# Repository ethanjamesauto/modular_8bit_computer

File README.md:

# Modular 8-bit Computer
This is the repository for an 8-bit computer system that is built using cards with a standardized interface. 

* [CPU card](processor_attempt_1)
* [Protoboard card](smaller_card_for_74_series)
  * This card contains an onboard clock generator, address and data registers/buffers, and a protoboard area for testing designs.
* [Bus interface modeling](digital)

Here's an example of a card:

## Current Bus Specification
```verilog
// The main bus wires (32+8=40 wires total)
// On the bus connector, all buses have LSBs closer to the power pins and MSBs farther away
wire VCC_5V;
wire GND;
wire clk;			      // generated by motherboard clock generator
wire rst_n;			    // probably a button on the motherboard
wire VCC_3V3;
wire we_n;			      // active LOW
wire oe_n;			      // active LOW
wire int_n;			    // pulled up by motherboard; driven down by any peripheral (could be used for interrupts)
wire [7:0] data;
wire [15:0] addr;	  // 64k address space is suppored by default. More address bits may be added later
wire [7:0] aux_bus;
```

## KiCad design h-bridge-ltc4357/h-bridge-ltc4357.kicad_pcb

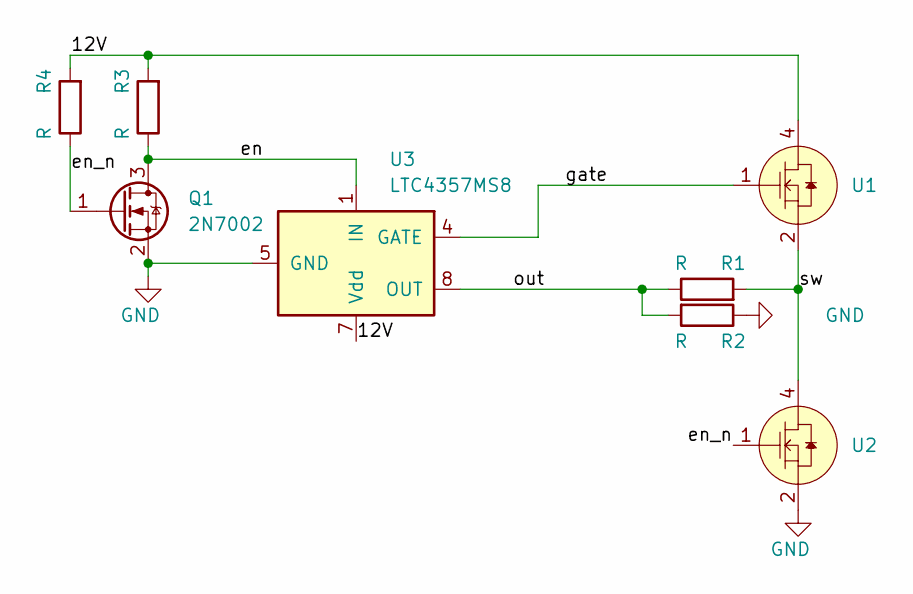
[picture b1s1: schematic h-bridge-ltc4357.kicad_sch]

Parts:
Q1: 2N7002; SOT-23
R1, R2, R3, R4: R; R_0603_1608Metric_Pad0.98x0.95mm_HandSolder
U1, U2: TO-263-6
U3: LTC4357MS8; MSOP-8_3x3mm_P0.65mm

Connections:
/12V: R3.2, R4.2, U1.4, U3.7 (Vdd)
/en: Q1.3 (D), R3.1, U3.1 (IN)
/en_n: Q1.1 (G), R4.1, U2.1
/gate: U1.1, U3.4 (GATE)
/out: R1.1, R2.2, U3.8 (OUT)
/sw: R1.2, U1.2, U1.3, U1.5, U1.6, U1.7, U2.4
GND: Q1.2 (S), R2.1, U2.2, U2.3, U2.5, U2.6, U2.7, U3.5 (GND)

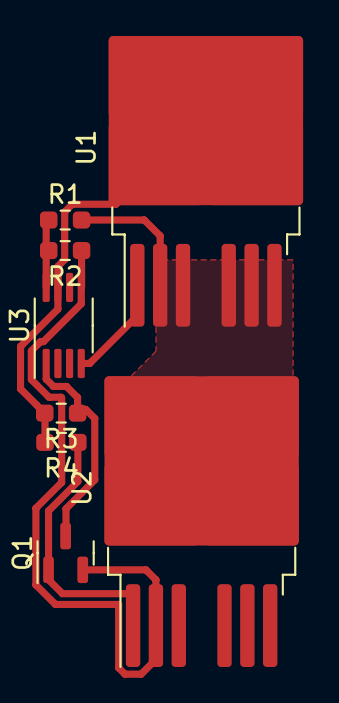
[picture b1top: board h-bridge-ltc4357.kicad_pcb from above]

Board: 2 copper layers, 8 parts (0 on the bottom side), 7 nets.

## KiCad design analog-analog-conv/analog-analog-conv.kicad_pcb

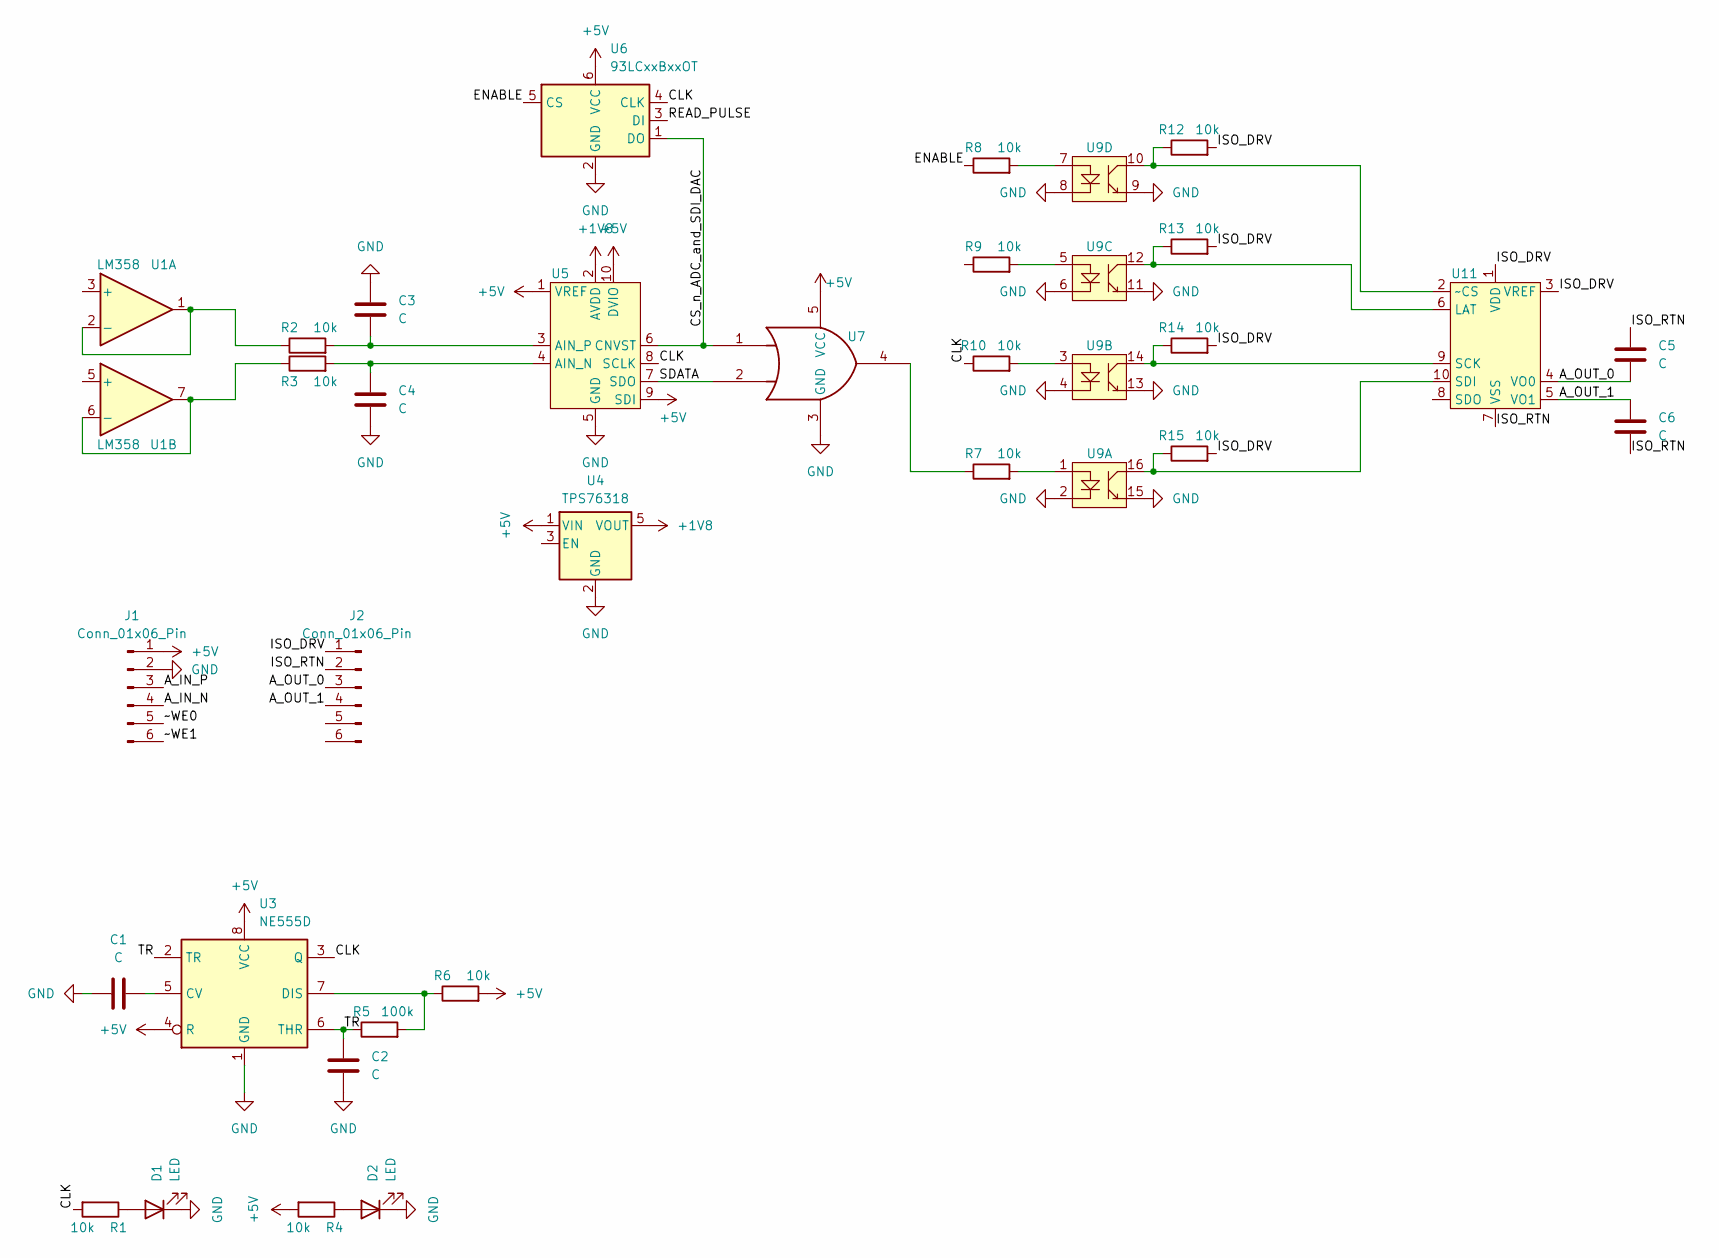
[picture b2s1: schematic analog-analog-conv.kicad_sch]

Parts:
C1, C2, C3, C4, C5, C6: C; C_0603_1608Metric_Pad1.08x0.95mm_HandSolder
D1, D2: LED; LED_0603_1608Metric_Pad1.05x0.95mm_HandSolder
J1, J2: Conn_01x06_Pin; PinHeader_1x06_P2.54mm_Vertical
R1, R2, R3, R4, R6, R7, R8, R9, R10, R12, R13, R14, R15: 10k; R_0603_1608Metric_Pad0.98x0.95mm_HandSolder
R5: 100k; R_0603_1608Metric_Pad0.98x0.95mm_HandSolder
U1: LM358; SOIC-8_3.9x4.9mm_P1.27mm
U3: NE555D; SOIC-8_3.9x4.9mm_P1.27mm
U4: TPS76318; SOT-23-5
U5: MCP33141D; MSOP-10_3x3mm_P0.5mm
U6: 93LCxxBxxOT; SOT-23-6
U7: 74LVC1G32; SOT-23-5_HandSoldering
U9: SOIC-16_4.55x10.3mm_P1.27mm
U11: MSOP-10_3x3mm_P0.5mm

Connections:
+1V8: U4.5 (VOUT), U5.2 (AVDD)
+5V: J1.1, R4.2, R6.2, U3.4 (R), U3.8 (VCC), U4.1 (VIN), U5.1 (VREF), U5.9 (SDI), U5.10 (DVIO), U6.6 (VCC), U7.5 (VCC)
/A_IN_N: J1.4
/A_IN_P: J1.3
/A_OUT_0: C5.1, J2.3, U11.4 (VO0)
/A_OUT_1: C6.2, J2.4, U11.5 (VO1)
/CLK: R1.2, R10.1, U3.3 (Q), U5.8 (SCLK), U6.4 (CLK)
/CS_n_ADC_and_SDI_DAC: U5.6 (CNVST), U6.1 (DO), U7.1
/ENABLE: R8.1, U6.5 (CS)
/ISO_DRV: J2.1, R12.2, R13.2, R14.2, R15.2, U11.1 (VDD), U11.3 (VREF)
/ISO_RTN: C5.2, C6.1, J2.2, U11.7 (VSS)
/READ_PULSE: U6.3 (DI)
/SDATA: U5.7 (SDO), U7.2
/TR: C2.1, R5.1, U3.2 (TR), U3.6 (THR)
/~WE0: J1.5
/~WE1: J1.6
GND: C1.1, C2.2, C3.2, C4.1, D1.1 (K), D2.1 (K), J1.2, U3.1 (GND), U4.2 (GND), U5.5 (GND), U6.2 (GND), U7.3 (GND), U9.2, U9.4, U9.6, U9.8, U9.9, U9.11, U9.13, U9.15
unnamed: D1.2 (A), R1.1
unnamed: D2.2 (A), R4.1
unnamed: R7.1, U7.4
unnamed: R7.2, U9.1
unnamed: R8.2, U9.7
unnamed: R9.2, U9.5
unnamed: R10.2, U9.3
unnamed: R2.1, U1.1, U1.2 (-)
unnamed: R3.1, U1.6 (-), U1.7
unnamed: C1.2, U3.5 (CV)
unnamed: R5.2, R6.1, U3.7 (DIS)
unnamed: C4.2, R3.2, U5.4 (AIN_N)
unnamed: C3.1, R2.2, U5.3 (AIN_P)
unnamed: R13.1, U9.12, U11.6 (LAT)
unnamed: R14.1, U9.14, U11.9 (SCK)
unnamed: R15.1, U9.16, U11.10 (SDI)
unnamed: R12.1, U9.10, U11.2 (~CS)

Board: 2 copper layers, 32 parts (7 on the bottom side), 29 nets, no tracks yet.

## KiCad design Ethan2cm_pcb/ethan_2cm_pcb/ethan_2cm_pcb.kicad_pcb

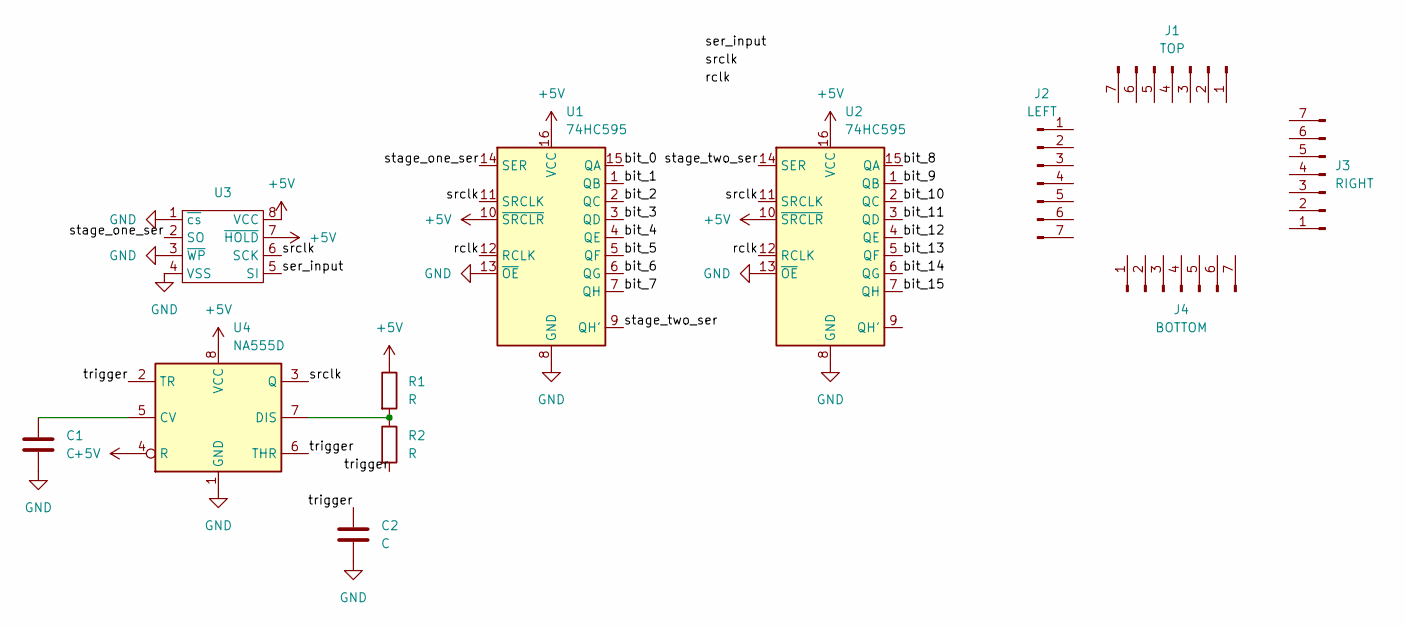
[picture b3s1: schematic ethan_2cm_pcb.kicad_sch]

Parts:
C1, C2: C; C_0603_1608Metric
J1: TOP; PinHeader_1x07_P2.54mm_Vertical
J2: LEFT; PinHeader_1x07_P2.54mm_Vertical
J3: RIGHT; PinHeader_1x07_P2.54mm_Vertical
J4: BOTTOM; PinHeader_1x07_P2.54mm_Vertical
R1, R2: R; C_0603_1608Metric
U1, U2: 74HC595; SOIC-16_3.9x9.9mm_P1.27mm
U3: DIP-8_W7.62mm
U4: NA555D; SOIC-8_3.9x4.9mm_P1.27mm

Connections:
+5V: R1.1, U1.10 (~SRCLR), U1.16 (VCC), U2.10 (~SRCLR), U2.16 (VCC), U3.7 (~HOLD), U3.8 (VCC), U4.4 (R), U4.8 (VCC)
/bit_0: U1.15 (QA)
/bit_1: U1.1 (QB)
/bit_2: U1.2 (QC)
/bit_3: U1.3 (QD)
/bit_4: U1.4 (QE)
/bit_5: U1.5 (QF)
/bit_6: U1.6 (QG)
/bit_7: U1.7 (QH)
/bit_8: U2.15 (QA)
/bit_9: U2.1 (QB)
/bit_10: U2.2 (QC)
/bit_11: U2.3 (QD)
/bit_12: U2.4 (QE)
/bit_13: U2.5 (QF)
/bit_14: U2.6 (QG)
/bit_15: U2.7 (QH)
/rclk: U1.12 (RCLK), U2.12 (RCLK)
/ser_input: U3.5 (SI)
/srclk: U1.11 (SRCLK), U2.11 (SRCLK), U3.6 (SCK), U4.3 (Q)
/stage_one_ser: U1.14 (SER), U3.2 (SO)
/stage_two_ser: U1.9 (QH'), U2.14 (SER)
/trigger: C2.1, R2.2, U4.2 (TR), U4.6 (THR)
GND: C1.2, C2.2, U1.8 (GND), U1.13 (~OE), U2.8 (GND), U2.13 (~OE), U3.1 (~cs), U3.3 (~WP), U3.4 (VSS), U4.1 (GND)
unnamed: C1.1, U4.5 (CV)
unnamed: R1.2, R2.1, U4.7 (DIS)

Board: 2 copper layers, 12 parts (0 on the bottom side), 9 nets, no tracks yet.

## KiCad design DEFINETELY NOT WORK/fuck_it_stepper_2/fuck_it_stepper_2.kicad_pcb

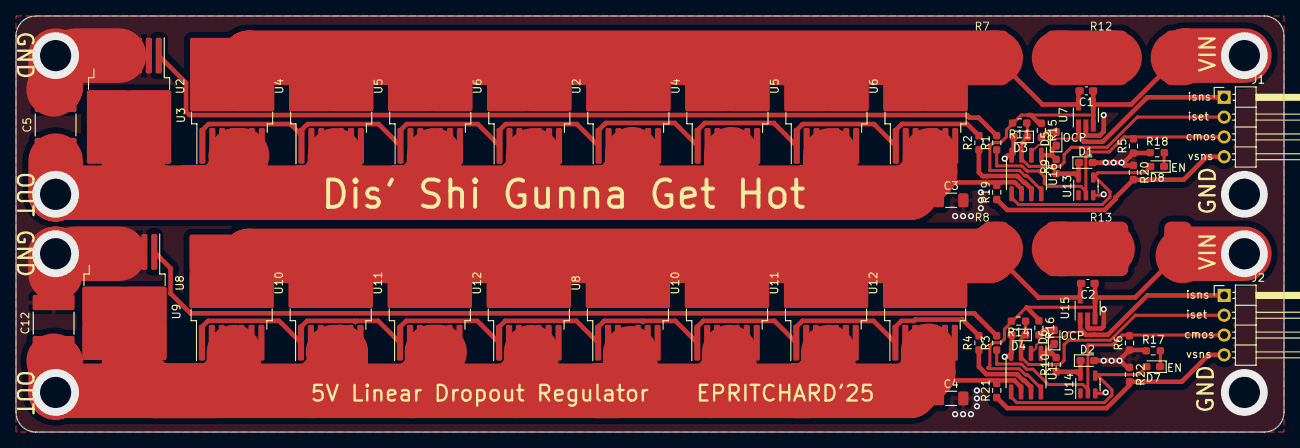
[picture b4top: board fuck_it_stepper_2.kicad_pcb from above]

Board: 2 copper layers, 162.6 x 53.3 mm, 62 parts (0 on the bottom side), 32 nets.

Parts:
C1, C2: C; C_0603_1608Metric_Pad1.08x0.95mm_HandSolder
C3, C4: C; C_1206_3216Metric_Pad1.33x1.80mm_HandSolder
C5, C12: C; C_2220_5650Metric_Pad1.97x5.40mm_HandSolder
D1, D2, D3, D4: D_Zener; D_0603_1608Metric_Pad1.05x0.95mm_HandSolder
D5, D6, D7, D8: LED; LED_0603_1608Metric_Pad1.05x0.95mm_HandSolder
J1, J2: Conn_01x04; PinHeader_1x04_P2.54mm_Horizontal
R1, R2, R3, R4, R5, R6, R9, R10, R11, R14, R15, R16, R17, R18, R19, R20, R21, R22: R; R_0603_1608Metric_Pad0.98x0.95mm_HandSolder
R7, R8, R12, R13: 4527
U1, U16: LM358; SOIC-8_3.9x4.9mm_P1.27mm
U2, U2#2, U3, U4, U4#2, U5, U5#2, U6, U6#2, U8, U8#2, U9, U10, U10#2, U11, U11#2, U12, U12#2: TO-263-6
U7, U15: SOT-23-5_HandSoldering
U13, U14: SN74LVC1G14DBV; SOT-23-5

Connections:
+12V: C1.1, C2.1, R11.2, R12.2, R13.2, R14.2, R15.1, R16.1, U1.8 (V+), U7.3 (Vs), U7.4 (IN+), U15.3 (Vs), U15.4 (IN+), U16.8 (V+)
/H-bridge/5v_0: C3.1, C5.1, R19.2, U2.2, U2.3, U2.5, U2.6, U2.7, U2#2.2, U2#2.3, U2#2.5, U2#2.6, U2#2.7, U3.4, U4.2, U4.3, U4.5, U4.6, U4.7, U4#2.2, U4#2.3, U4#2.5, U4#2.6, U4#2.7, U5.2, U5.3, U5.5, U5.6, U5.7, U5#2.2, U5#2.3, U5#2.5, U5#2.6, U5#2.7, U6.2, U6.3, U6.5, U6.6, U6.7, U6#2.2, U6#2.3, U6#2.5, U6#2.6, U6#2.7, U16.6 (-)
/H-bridge/5v_1: C4.1, C12.1, R21.2, U1.6 (-), U8.2, U8.3, U8.5, U8.6, U8.7, U8#2.2, U8#2.3, U8#2.5, U8#2.6, U8#2.7, U9.4, U10.2, U10.3, U10.5, U10.6, U10.7, U10#2.2, U10#2.3, U10#2.5, U10#2.6, U10#2.7, U11.2, U11.3, U11.5, U11.6, U11.7, U11#2.2, U11#2.3, U11#2.5, U11#2.6, U11#2.7, U12.2, U12.3, U12.5, U12.6, U12.7, U12#2.2, U12#2.3, U12#2.5, U12#2.6, U12#2.7
/H-bridge/enable_0: D8.2 (A), U13.4, U16.5 (+)
/H-bridge/enable_1: D7.2 (A), U1.5 (+), U14.4
/H-bridge/enable_n_0_cmos: J1.3, R1.1, R5.2, U13.2
/H-bridge/enable_n_1_cmos: J2.3, R3.1, R6.2, U14.2
/H-bridge/gate_0: R2.2, U2.1, U2#2.1, U4.1, U4#2.1, U5.1, U5#2.1, U6.1, U6#2.1
/H-bridge/gate_1: R4.2, U8.1, U8#2.1, U10.1, U10#2.1, U11.1, U11#2.1, U12.1, U12#2.1
/H-bridge/inject_OC_thresh_0: D3.1 (K), J1.2, R11.1, U16.3 (+)
/H-bridge/inject_OC_thresh_1: D4.1 (K), J2.2, R14.1, U1.3 (+)
/H-bridge/input_i_sns_0: J1.1, U7.1 (OUT), U16.2 (-)
/H-bridge/input_i_sns_1: J2.1, U1.2 (-), U15.1 (OUT)
/H-bridge/sw_0_oc_n: D5.1 (K), R9.2, U16.1
/H-bridge/sw_1_oc_n: D6.1 (K), R10.2, U1.1
/H-bridge/v_sns_0: J1.4, R19.1, R20.2
/H-bridge/v_sns_1: J2.4, R21.1, R22.2
GND: C3.2, C4.2, C5.2, C12.2, D1.2 (A), D2.2 (A), D3.2 (A), D4.2 (A), R5.1, R6.1, R17.1, R18.1, R20.1, R22.1, U1.4 (V-), U3.2, U3.3, U3.5, U3.6, U3.7, U7.2 (GND), U9.2, U9.3, U9.5, U9.6, U9.7, U13.3 (GND), U14.3 (GND), U15.2 (GND), U16.4 (V-)
unnamed: D1.1 (K), R9.1, U13.5 (VCC)
unnamed: D2.1 (K), R10.1, U14.5 (VCC)
unnamed: D5.2 (A), R15.2
unnamed: D6.2 (A), R16.2
unnamed: D7.1 (K), R17.2
unnamed: D8.1 (K), R18.2
unnamed: R1.2, U3.1
unnamed: R2.1, U16.7
unnamed: R3.2, U9.1
unnamed: R4.1, U1.7
unnamed: R7.2, R12.1
unnamed: R8.2, R13.1
unnamed: C1.2, R7.1, U2.4, U2#2.4, U4.4, U4#2.4, U5.4, U5#2.4, U6.4, U6#2.4, U7.5 (IN-)
unnamed: C2.2, R8.1, U8.4, U8#2.4, U10.4, U10#2.4, U11.4, U11#2.4, U12.4, U12#2.4, U15.5 (IN-)

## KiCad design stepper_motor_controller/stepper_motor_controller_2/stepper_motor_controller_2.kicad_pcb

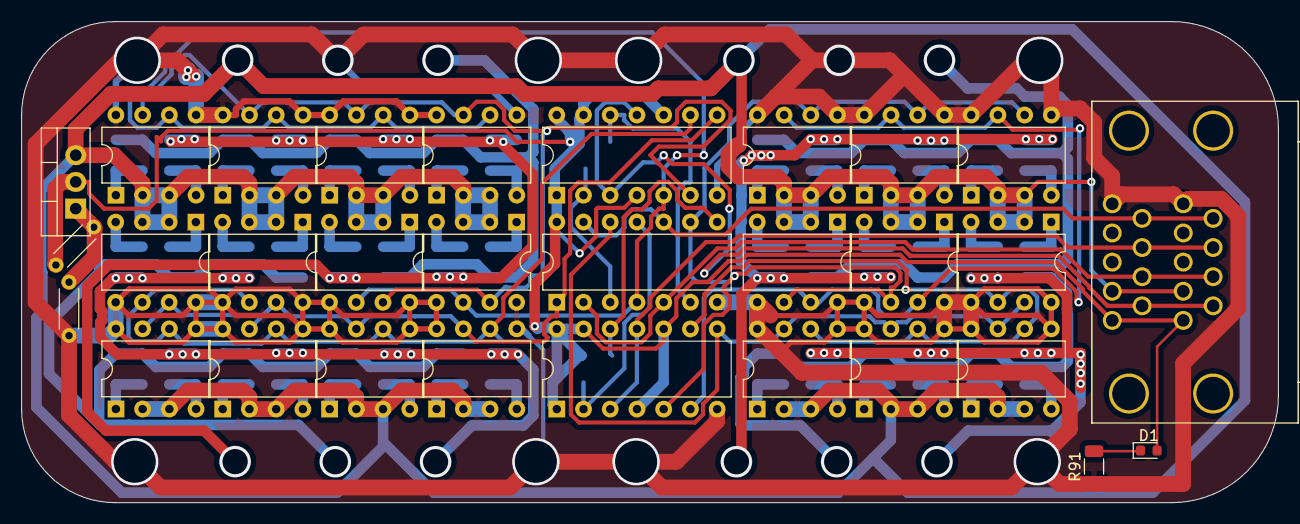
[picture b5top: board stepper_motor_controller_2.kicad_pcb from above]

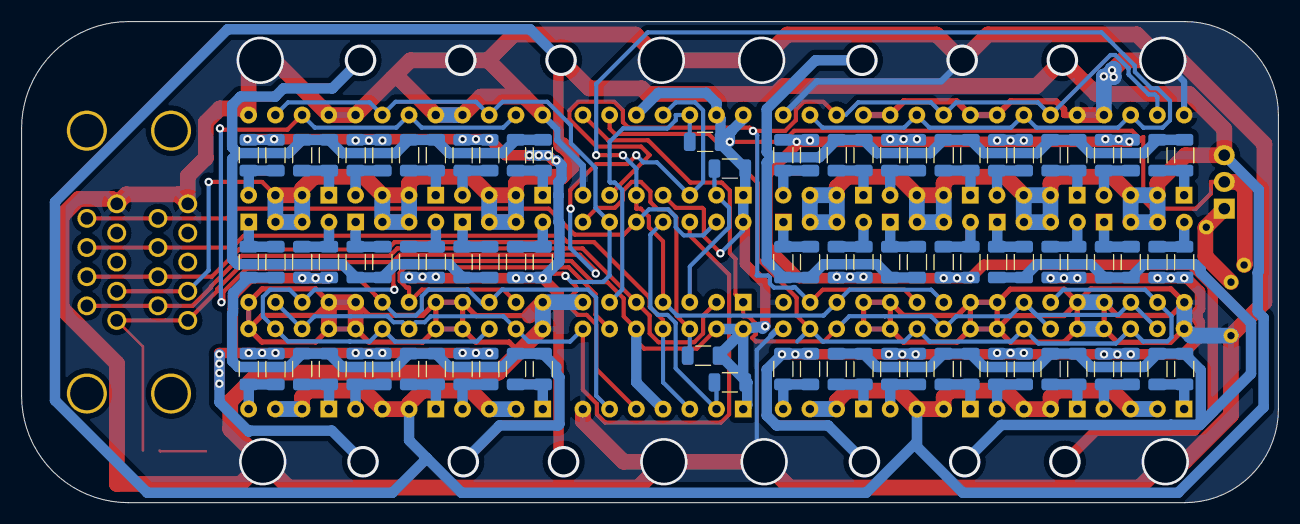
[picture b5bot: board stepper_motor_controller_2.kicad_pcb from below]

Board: 2 copper layers, 119.4 x 45.7 mm, 118 parts (88 on the bottom side), 71 nets.

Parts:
D1: LED; LED_0603_1608Metric
J2: 178-009-613R571
R1, R2, R3, R4, R5, R6, R7, R8, R9, R10, R11, R12, R13, R14, R15, R16, R19, R20, R21, R22, R23, R24, R25, R26, R27, R28, R29, R30, R31, R32, R33, R34, R35, R36, R39, R40, R41, R42, R43, R44, R45, R46, R47, R48, R49, R50, R53, R54, R55, R56, R57, R58, R59, R60, R61, R62, R63, R64, R65, R66, R67, R68, R69, R70, R71, R72, R73, R74, R75, R76, R77, R78, R79, R80, R81, R82, R83, R84, R85, R86, R87, R88, R89, R90, R91: 1; R_1206_3216Metric
R17, R18, R51, R52: 5k; R_1206_3216Metric
R37: 820; R_Axial_DIN0204_L3.6mm_D1.6mm_P5.08mm_Horizontal
R38: 220; R_Axial_DIN0204_L3.6mm_D1.6mm_P5.08mm_Horizontal
U1, U28: 74LS74; DIP-14_W7.62mm
U2, U4, U5, U6, U7, U8, U9, U10, U12, U13, U14, U15, U16, U17, U18, U19, U20, U24, U25, U26, U27: DIP-8_W7.62mm
U3: 74LS136; DIP-14_W7.62mm
U11: LM317_TO-220; TO-220-3_Vertical

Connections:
+5V: D1.2 (A), J2.1A, J2.1B, R17.2, R18.2, R37.1, R51.2, R52.2, U1.1 (~R), U1.4 (~S), U1.10 (~S), U1.13 (~R), U1.14 (VCC), U3.14 (VCC), U11.2 (VO), U28.1 (~R), U28.4 (~S), U28.10 (~S), U28.13 (~R), U28.14 (VCC)
/A: R1.2, R5.2, R9.2, R13.2, R39.2, R41.2, R43.2, R47.2, R53.2, R55.2, R57.2, R59.2
/A_logic: U1.5 (Q), U2.6 (IA), U3.4, U5.6 (IA), U7.6 (IA), U9.6 (IA), U24.6 (IA), U26.6 (IA)
/A_n_logic: U1.6 (~Q), U2.7 (IB), U5.7 (IB), U7.7 (IB), U9.7 (IB), U24.7 (IB), U26.7 (IB)
/B: R2.2, R6.2, R10.2, R14.2, R40.2, R42.2, R44.2, R48.2, R54.2, R56.2, R58.2, R60.2
/B_logic: U1.9 (Q), U4.6 (IA), U6.6 (IA), U8.6 (IA), U10.6 (IA), U25.6 (IA), U27.6 (IA)
/B_n_logic: U1.8 (~Q), U3.1, U4.7 (IB), U6.7 (IB), U8.7 (IB), U10.7 (IB), U25.7 (IB), U27.7 (IB)
/C: R3.2, R7.2, R11.2, R15.2, R45.2, R49.2, R61.2, R63.2, R65.2, R67.2, R69.2, R71.2
/CLOCK_lower: J2.8A, J2.8B, U28.3 (C), U28.11 (C)
/CLOCK_upper: J2.6A, J2.6B, U1.3 (C), U1.11 (C)
/D: R4.2, R8.2, R12.2, R16.2, R46.2, R50.2, R62.2, R64.2, R66.2, R68.2, R70.2, R72.2
/DIRECTION_lower: J2.9A, J2.9B, U3.10, U3.13
/DIRECTION_upper: J2.7A, J2.7B, U3.2, U3.5
/E: R19.2, R23.2, R27.2, R31.2, R35.2, R73.2, R75.2, R77.2, R79.2, R81.2
/E_logic: U3.9, U12.6 (IA), U14.6 (IA), U16.6 (IA), U18.6 (IA), U20.6 (IA), U28.5 (Q)
/E_n_logic: U12.7 (IB), U14.7 (IB), U16.7 (IB), U18.7 (IB), U20.7 (IB), U28.6 (~Q)
/F: R20.2, R24.2, R28.2, R32.2, R36.2, R74.2, R76.2, R78.2, R80.2, R82.2
/F_logic: U13.6 (IA), U15.6 (IA), U17.6 (IA), U19.6 (IA), U28.9 (Q)
/F_n_logic: U3.12, U13.7 (IB), U15.7 (IB), U17.7 (IB), U19.7 (IB), U28.8 (~Q)
/G: R21.2, R25.2, R29.2, R33.2, R83.2, R85.2, R87.2, R89.2
/H: R22.2, R26.2, R30.2, R34.2, R84.2, R86.2, R88.2, R90.2
GND: J2.5A, J2.5B, R38.2, R91.1, U1.7 (GND), U2.5 (GND), U2.8 (GND), U3.7 (GND), U4.5 (GND), U4.8 (GND), U5.5 (GND), U5.8 (GND), U6.5 (GND), U6.8 (GND), U7.5 (GND), U7.8 (GND), U8.5 (GND), U8.8 (GND), U9.5 (GND), U9.8 (GND), U10.5 (GND), U10.8 (GND), U12.5 (GND), U12.8 (GND), U13.5 (GND), U13.8 (GND), U14.5 (GND), U14.8 (GND), U15.5 (GND), U15.8 (GND), U16.5 (GND), U16.8 (GND), U17.5 (GND), U17.8 (GND), U18.5 (GND), U18.8 (GND), U19.5 (GND), U19.8 (GND), U20.5 (GND), U20.8 (GND), U24.5 (GND), U24.8 (GND), U25.5 (GND), U25.8 (GND), U26.5 (GND), U26.8 (GND), U27.5 (GND), U27.8 (GND), U28.7 (GND)
unnamed: D1.1 (K), R91.2
unnamed: R1.1, R39.1, U2.1 (OA)
unnamed: R2.1, R40.1, U2.4 (OA)
unnamed: R3.1, R71.1, U4.1 (OA)
unnamed: R4.1, R72.1, U4.4 (OA)
unnamed: R10.1, R54.1, U7.4 (OA)
unnamed: R11.1, R67.1, U8.1 (OA)
unnamed: R12.1, R68.1, U8.4 (OA)
unnamed: R13.1, R55.1, U9.1 (OA)
unnamed: R14.1, R56.1, U9.4 (OA)
unnamed: R15.1, R65.1, U10.1 (OA)
unnamed: R16.1, R66.1, U10.4 (OA)
unnamed: R19.1, R73.1, U12.1 (OA)
unnamed: R20.1, R74.1, U12.4 (OA)
unnamed: R21.1, R89.1, U13.1 (OA)
unnamed: R22.1, R90.1, U13.4 (OA)
unnamed: R23.1, R75.1, U14.1 (OA)
unnamed: R24.1, R76.1, U14.4 (OA)
unnamed: R25.1, R87.1, U15.1 (OA)
unnamed: R26.1, R88.1, U15.4 (OA)
unnamed: R27.1, R77.1, U16.1 (OA)
unnamed: R28.1, R78.1, U16.4 (OA)
unnamed: R29.1, R85.1, U17.1 (OA)
unnamed: R30.1, R86.1, U17.4 (OA)
unnamed: R31.1, R79.1, U18.1 (OA)
unnamed: R32.1, R80.1, U18.4 (OA)
unnamed: R33.1, R83.1, U19.1 (OA)
unnamed: R34.1, R84.1, U19.4 (OA)
unnamed: R35.1, R81.1, U20.1 (OA)
unnamed: R36.1, R82.1, U20.4 (OA)
unnamed: R5.1, R41.1, U5.1 (OA)
unnamed: R6.1, R42.1, U5.4 (OA)
unnamed: R43.1, R57.1, U24.1 (OA)
unnamed: R44.1, R58.1, U24.4 (OA)
unnamed: R45.1, R63.1, U25.1 (OA)
unnamed: R46.1, R64.1, U25.4 (OA)
unnamed: R47.1, R59.1, U26.1 (OA)
unnamed: R48.1, R60.1, U26.4 (OA)
unnamed: R49.1, R61.1, U27.1 (OA)
unnamed: R50.1, R62.1, U27.4 (OA)
unnamed: R9.1, R53.1, U7.1 (OA)
unnamed: R7.1, R69.1, U6.1 (OA)
unnamed: R8.1, R70.1, U6.4 (OA)
unnamed: R18.1, U1.2 (D), U3.3
unnamed: R17.1, U1.12 (D), U3.6
unnamed: R37.2, R38.1, U11.1 (ADJ)
unnamed: R52.1, U3.11, U28.2 (D)
unnamed: R51.1, U3.8, U28.12 (D)
VCC: J2.2A, J2.2B, U2.2 (VCC), U2.3 (VCC), U4.2 (VCC), U4.3 (VCC), U5.2 (VCC), U5.3 (VCC), U6.2 (VCC), U6.3 (VCC), U7.2 (VCC), U7.3 (VCC), U8.2 (VCC), U8.3 (VCC), U9.2 (VCC), U9.3 (VCC), U10.2 (VCC), U10.3 (VCC), U11.3 (VI), U12.2 (VCC), U12.3 (VCC), U13.2 (VCC), U13.3 (VCC), U14.2 (VCC), U14.3 (VCC), U15.2 (VCC), U15.3 (VCC), U16.2 (VCC), U16.3 (VCC), U17.2 (VCC), U17.3 (VCC), U18.2 (VCC), U18.3 (VCC), U19.2 (VCC), U19.3 (VCC), U20.2 (VCC), U20.3 (VCC), U24.2 (VCC), U24.3 (VCC), U25.2 (VCC), U25.3 (VCC), U26.2 (VCC), U26.3 (VCC), U27.2 (VCC), U27.3 (VCC)

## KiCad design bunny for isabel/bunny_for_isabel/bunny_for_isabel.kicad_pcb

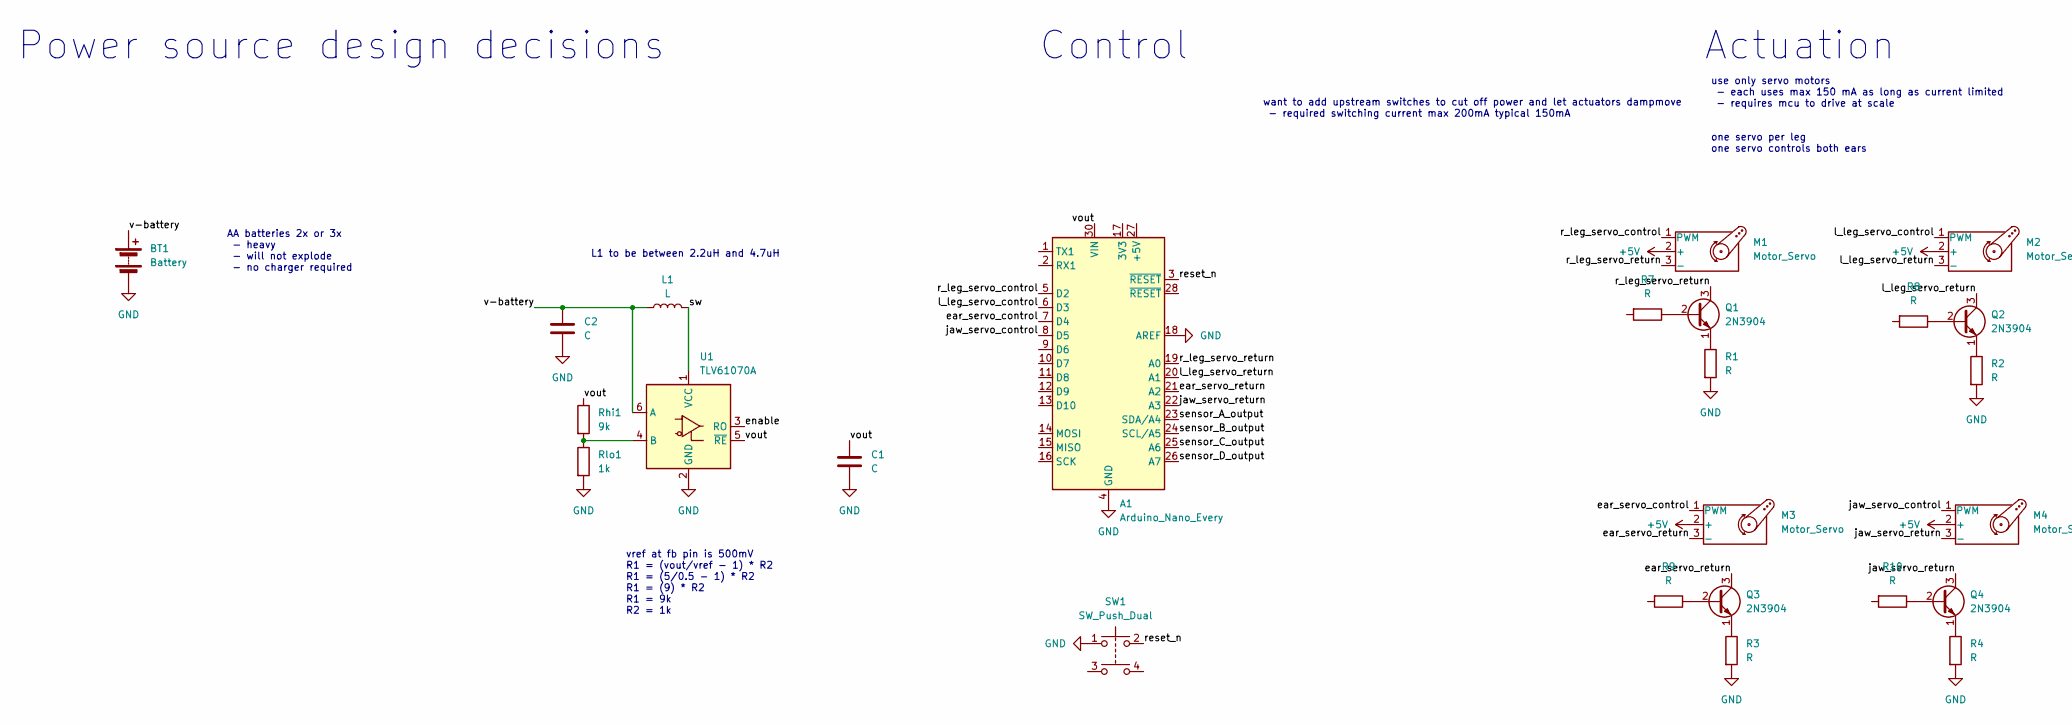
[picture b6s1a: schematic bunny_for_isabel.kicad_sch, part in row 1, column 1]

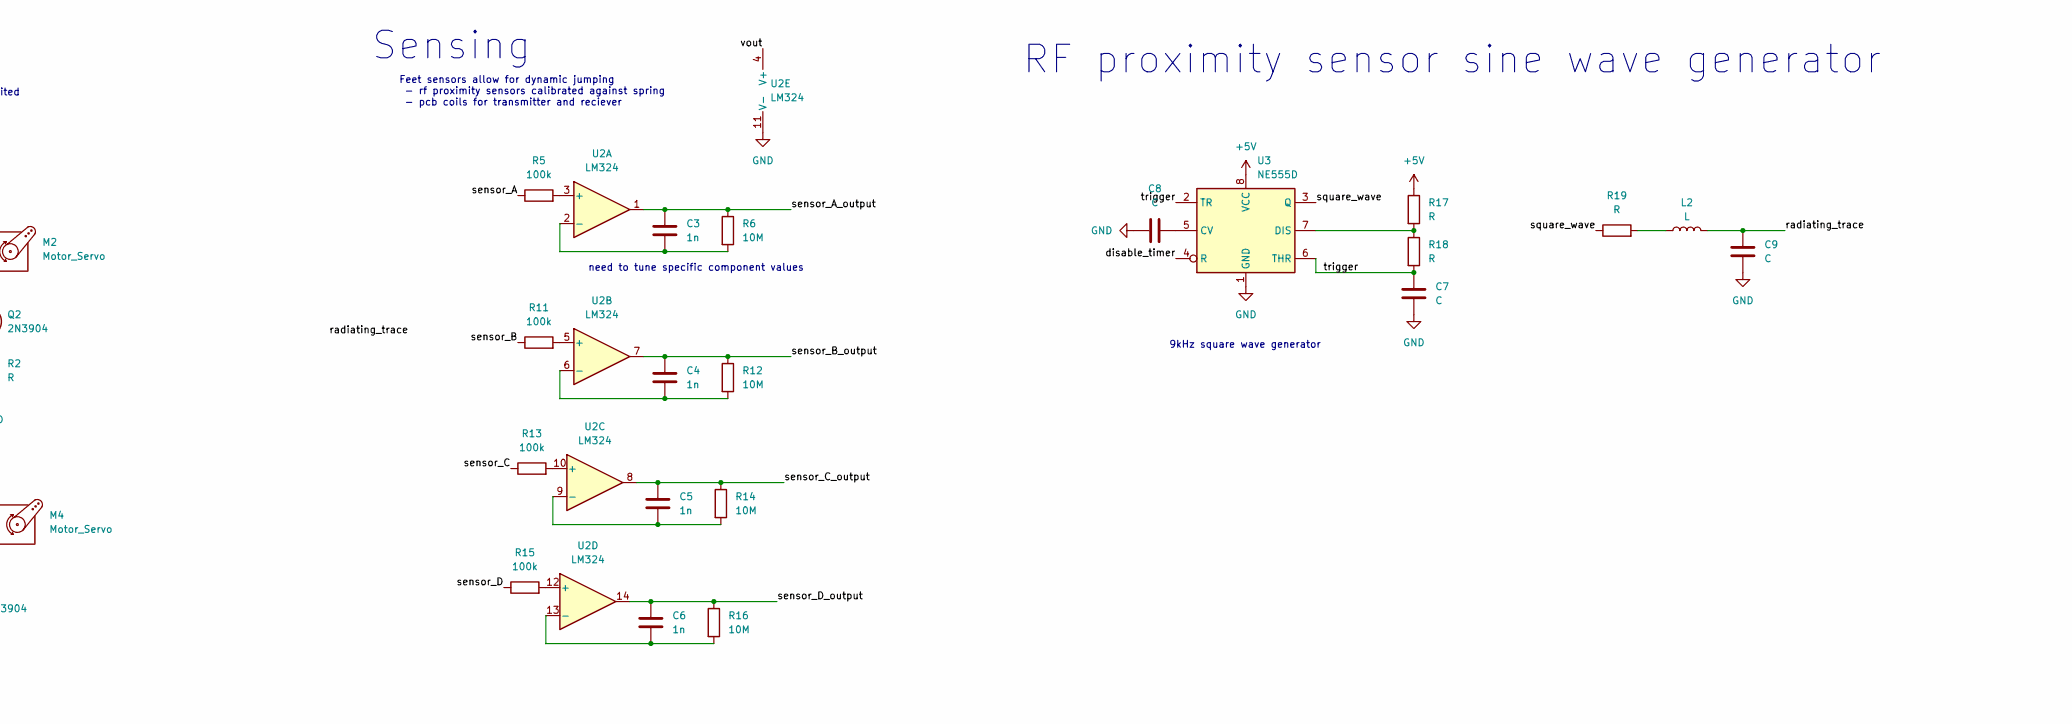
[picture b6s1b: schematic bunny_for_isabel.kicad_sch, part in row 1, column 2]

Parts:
A1: Arduino_Nano_Every; Arduino_Nano
BT1: Battery; PinHeader_1x02_P2.54mm_Vertical
C1, C2, C7, C8, C9: C; R_0603_1608Metric_Pad0.98x0.95mm_HandSolder
C3, C4, C5, C6: 1n; R_0603_1608Metric_Pad0.98x0.95mm_HandSolder
L1, L2: L
M1, M2, M3, M4: Motor_Servo; PinHeader_1x03_P2.54mm_Vertical
Q1, Q2, Q3, Q4: 2N3904; TO-92_Inline
R1, R2, R3, R4, R7, R8, R9, R10, R17, R18, R19: R; R_0603_1608Metric_Pad0.98x0.95mm_HandSolder
R5, R11, R13, R15: 100k; R_0603_1608Metric_Pad0.98x0.95mm_HandSolder
R6, R12, R14, R16: 10M; R_0603_1608Metric_Pad0.98x0.95mm_HandSolder
Rhi1: 9k; R_0603_1608Metric_Pad0.98x0.95mm_HandSolder
Rlo1: 1k; R_0603_1608Metric_Pad0.98x0.95mm_HandSolder
SW1: SW_Push_Dual; SW_DIP_SPSTx02_Slide_KingTek_DSHP02TJ_W5.25mm_P1.27mm_JPin
U1: TLV61070A; SOT-23-6
U2: LM324; DIP-14_W7.62mm
U3: NE555D; SOIC-8_3.9x4.9mm_P1.27mm

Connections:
+5V: M1.2 (+), M2.2 (+), M3.2 (+), M4.2 (+), R17.1, U3.8 (VCC)
/disable_timer: U3.4 (R)
/ear_servo_control: A1.7 (D4), M3.1 (PWM)
/ear_servo_return: A1.21 (A2), M3.3 (-), Q3.3 (C)
/enable: U1.3 (RO)
/jaw_servo_control: A1.8 (D5), M4.1 (PWM)
/jaw_servo_return: A1.22 (A3), M4.3 (-), Q4.3 (C)
/l_leg_servo_control: A1.6 (D3), M2.1 (PWM)
/l_leg_servo_return: A1.20 (A1), M2.3 (-), Q2.3 (C)
/r_leg_servo_control: A1.5 (D2), M1.1 (PWM)
/r_leg_servo_return: A1.19 (A0), M1.3 (-), Q1.3 (C)
/radiating_trace: C9.1, L2.2
/reset_n: A1.3 (~RESET), SW1.2
/sensor_A: R5.1
/sensor_A_output: A1.23 (SDA/A4), C3.1, R6.1, U2.1
/sensor_B: R11.1
/sensor_B_output: A1.24 (SCL/A5), C4.1, R12.1, U2.7
/sensor_C: R13.1
/sensor_C_output: A1.25 (A6), C5.1, R14.1, U2.8
/sensor_D: R15.1
/sensor_D_output: A1.26 (A7), C6.1, R16.1, U2.14
/square_wave: R19.1, U3.3 (Q)
/sw: L1.2, U1.1 (VCC)
/trigger: C7.1, R18.2, U3.2 (TR), U3.6 (THR)
/v-battery: BT1.1 (+), C2.1, L1.1, U1.6 (A)
/vout: A1.30 (VIN), C1.1, Rhi1.1, U1.5 (~RE), U2.4 (V+)
GND: A1.4 (GND), A1.18 (AREF), A1.29 (GND), BT1.2 (-), C1.2, C2.2, C7.2, C8.1, C9.2, R1.2, R2.2, R3.2, R4.2, Rlo1.2, SW1.1, U1.2 (GND), U2.11 (V-), U3.1 (GND)
unnamed: L2.1, R19.2
unnamed: Q1.2 (B), R7.1
unnamed: Q1.1 (E), R1.1
unnamed: Q2.2 (B), R8.1
unnamed: Q2.1 (E), R2.1
unnamed: Q3.2 (B), R9.1
unnamed: Q3.1 (E), R3.1
unnamed: Q4.2 (B), R10.1
unnamed: Q4.1 (E), R4.1
unnamed: Rhi1.2, Rlo1.1, U1.4 (B)
unnamed: R5.2, U2.3 (+)
unnamed: C3.2, R6.2, U2.2 (-)
unnamed: R11.2, U2.5 (+)
unnamed: C4.2, R12.2, U2.6 (-)
unnamed: R13.2, U2.10 (+)
unnamed: C5.2, R14.2, U2.9 (-)
unnamed: R15.2, U2.12 (+)
unnamed: C6.2, R16.2, U2.13 (-)
unnamed: C8.2, U3.5 (CV)
unnamed: R17.2, R18.1, U3.7 (DIS)

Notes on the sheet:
Actuation
Feet sensors allow for dynamic jumping - rf proximity sensors calibrated against spring - pcb coils for transmitter and reciever
L1 to be between 2.2uH and 4.7uH
need to tune specific component values
RF proximity sensor sine wave generator
want to add upstream switches to cut off power and let actuators dampmove - required switching current max 200mA typical 150mA
use only servo motors - each uses max 150 mA as long as current limited - requires mcu to drive at scale one servo per leg one servo controls both ears
Power source design decisions
Control
AA batteries 2x or 3x - heavy - will not explode - no charger required
9kHz square wave generator
Sensing
vref at fb pin is 500mV R1 = (vout/vref - 1) * R2 R1 = (5/0.5 - 1) * R2 R1 = (9) * R2 R1 = 9k R2 = 1k

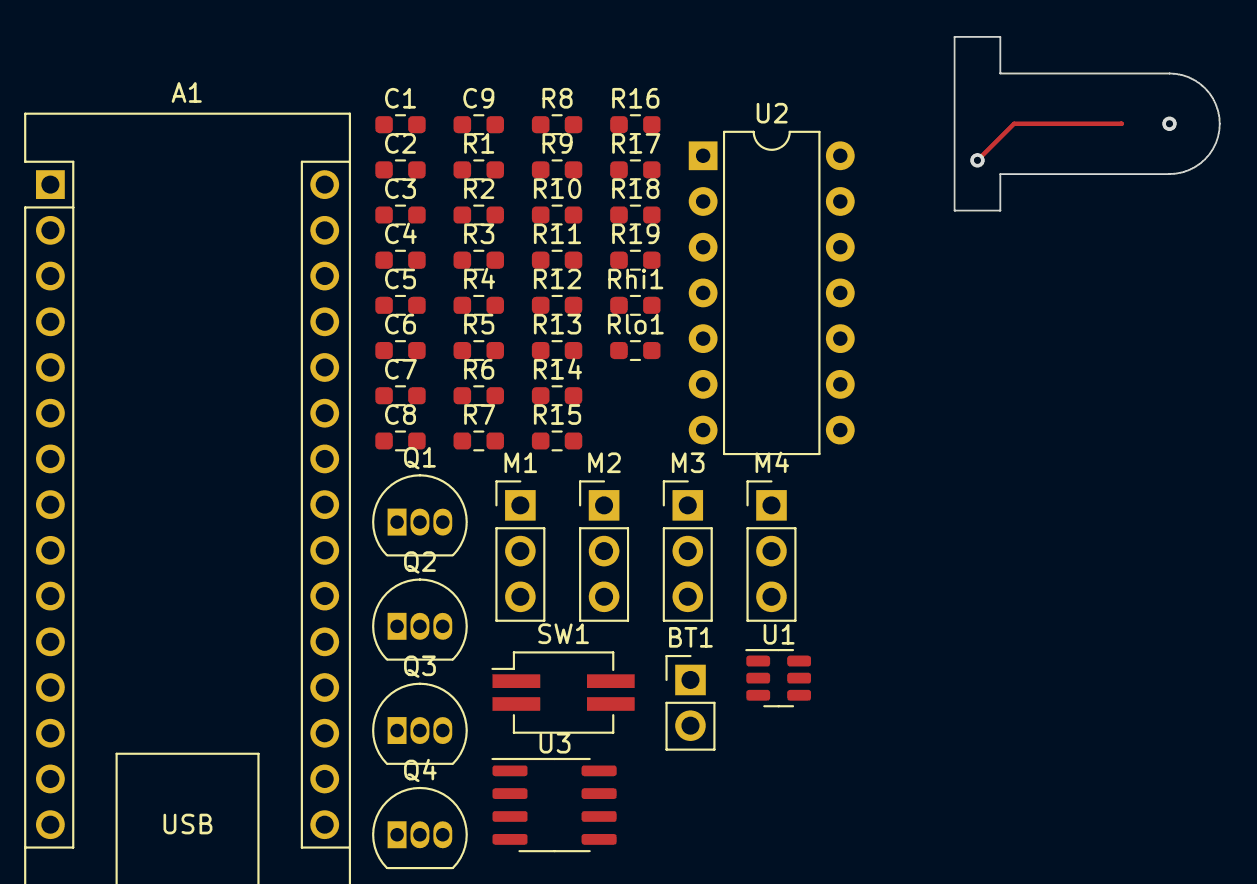
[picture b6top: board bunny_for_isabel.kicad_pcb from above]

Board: 2 copper layers, 44 parts (0 on the bottom side), 38 nets.
